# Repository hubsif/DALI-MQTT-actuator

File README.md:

# DALI-MQTT-actuator
An Arduino (Pro Mini) driven DALI actuator and MQTT gateway

More and documentation to follow ...

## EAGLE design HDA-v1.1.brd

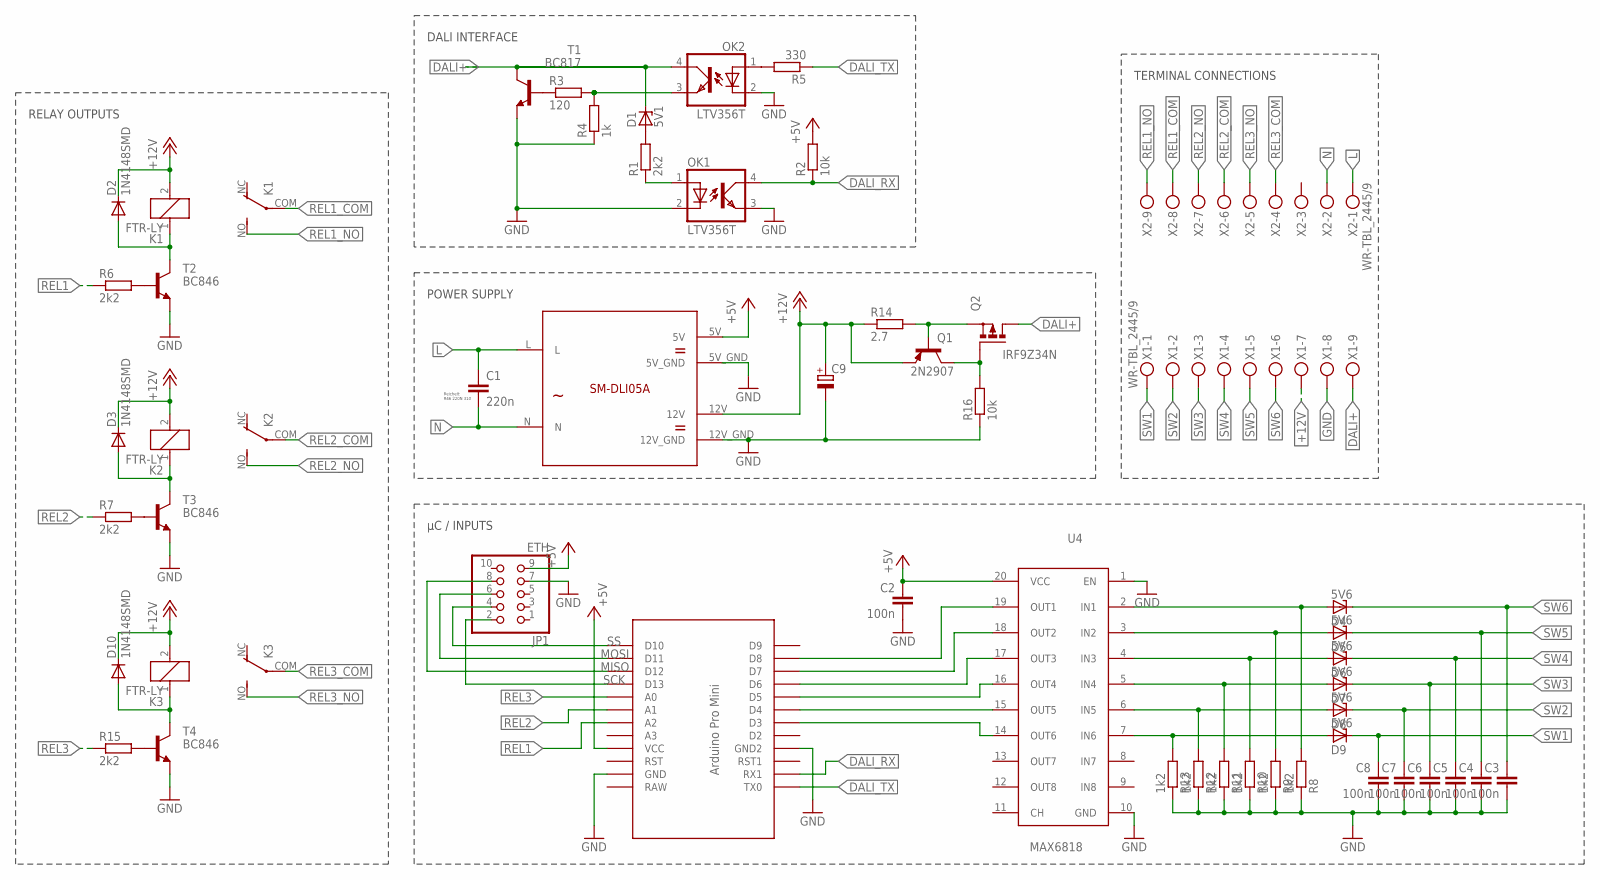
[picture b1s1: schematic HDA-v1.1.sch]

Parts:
C1: 220n; ECQUAAF224
C2, C3, C4, C5, C6, C7, C8: 100n; C1206K
C9: CPOL-EUSMCE; SMC_E
D1: 5V1; SOD80C
D2, D3, D10: 1N4148SMD; SOD80C
D4, D5, D6, D7, D8, D9: 5V6; SOD80C
JP1: ETH; 2X05
K1, K2, K3: FTR-LY; PE-FORM-C
OK1, OK2: LTV356T; SOP-4-2.54
Q1: 2N2907; SOT23-BEC
Q2: IRF9Z34N; TO220BV
R1, R6, R7, R15: 2k2; R1206
R2, R16: 10k; R1206
R3: 120; R1206
R4: 1k; R1206
R5: 330; R1206
R8, R9, R10, R11, R12, R13: 1k2; R1206
R14: 2.7; R1206
T1: BC817; SOT23-BEC
T2, T3, T4: BC846; SOT23
U1: SM-DLI05A
U2: ABK-PRO-MINI
U4: MAX6818; SSOP20
X1, X2: WR-TBL_2445/9

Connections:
+5V: C2.1, JP1.9, R2.2, U1.5V, U2.VCC, U4.20 (VCC)
+12V: C9.+, D2.C, D3.C, D10.C, K1.2, K2.2, K3.2, Q1.E, R14.1, U1.12V, X1.7
DALI+: D1.C, OK2.4 (COL), Q2.D, T1.C, X1.9
DALI_RX: OK1.4 (COL), R2.1, U2.RX1
DALI_TX: R5.1, U2.TX0
GND: C2.2, C3.2, C4.2, C5.2, C6.2, C7.2, C8.2, C9.-, JP1.7, OK1.2 (C), OK1.3 (EMIT), OK2.2 (C), R4.1, R8.1, R9.1, R10.1, R11.1, R12.1, R13.1, R16.1, T1.E, T2.2 (E), T3.2 (E), T4.2 (E), U1.5V_GND, U1.12V_GND, U2.GND, U2.GND1 (GND2), U4.1 (EN), U4.10 (GND), X1.8
L: C1.1, U1.L, X2.1
MISO: JP1.8, U2.D12
MOSI: JP1.6, U2.D11
N: C1.2, U1.N, X2.2
unnamed: D1.A, R1.2
unnamed: OK1.1 (A), R1.1
unnamed: Q1.B, Q2.S, R14.2
unnamed: R3.1, T1.B
unnamed: OK2.3 (EMIT), R3.2, R4.2
unnamed: Q1.C, Q2.G, R16.2
unnamed: OK2.1 (A), R5.2
unnamed: R15.2, T4.1 (B)
unnamed: R6.2, T2.1 (B)
unnamed: R7.2, T3.1 (B)
unnamed: D3.A, K2.1, T3.3 (C)
unnamed: D8.A, R12.2, U4.6 (IN5)
unnamed: D2.A, K1.1, T2.3 (C)
unnamed: D9.A, R13.2, U4.7 (IN6)
unnamed: D4.A, R8.2, U4.2 (IN1)
unnamed: D5.A, R9.2, U4.3 (IN2)
unnamed: D6.A, R10.2, U4.4 (IN3)
unnamed: D7.A, R11.2, U4.5 (IN4)
unnamed: D10.A, K3.1, T4.3 (C)
unnamed: U2.D5, U4.16 (OUT4)
unnamed: U2.D6, U4.17 (OUT3)
unnamed: U2.D7, U4.18 (OUT2)
unnamed: U2.D8, U4.19 (OUT1)
unnamed: U2.D4, U4.15 (OUT5)
unnamed: U2.D3, U4.14 (OUT6)
REL1: R6.1, U2.A2
REL1_COM: K1.COM, X2.8
REL1_NO: K1.NO (S), X2.9
REL2: R7.1, U2.A1
REL2_COM: K2.COM, X2.6
REL2_NO: K2.NO (S), X2.7
REL3: R15.1, U2.A0
REL3_COM: K3.COM, X2.4
REL3_NO: K3.NO (S), X2.5
SCK: JP1.2, U2.D13
SS: JP1.4, U2.D10
SW1: C8.1, D9.C, X1.1
SW2: C7.1, D8.C, X1.2
SW3: C6.1, D7.C, X1.3
SW4: C5.1, D6.C, X1.4
SW5: C4.1, D5.C, X1.5
SW6: C3.1, D4.C, X1.6

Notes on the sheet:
Reichelt: R46 220N 310
DALI INTERFACE
POWER SUPPLY
RELAY OUTPUTS
µC / INPUTS
TERMINAL CONNECTIONS

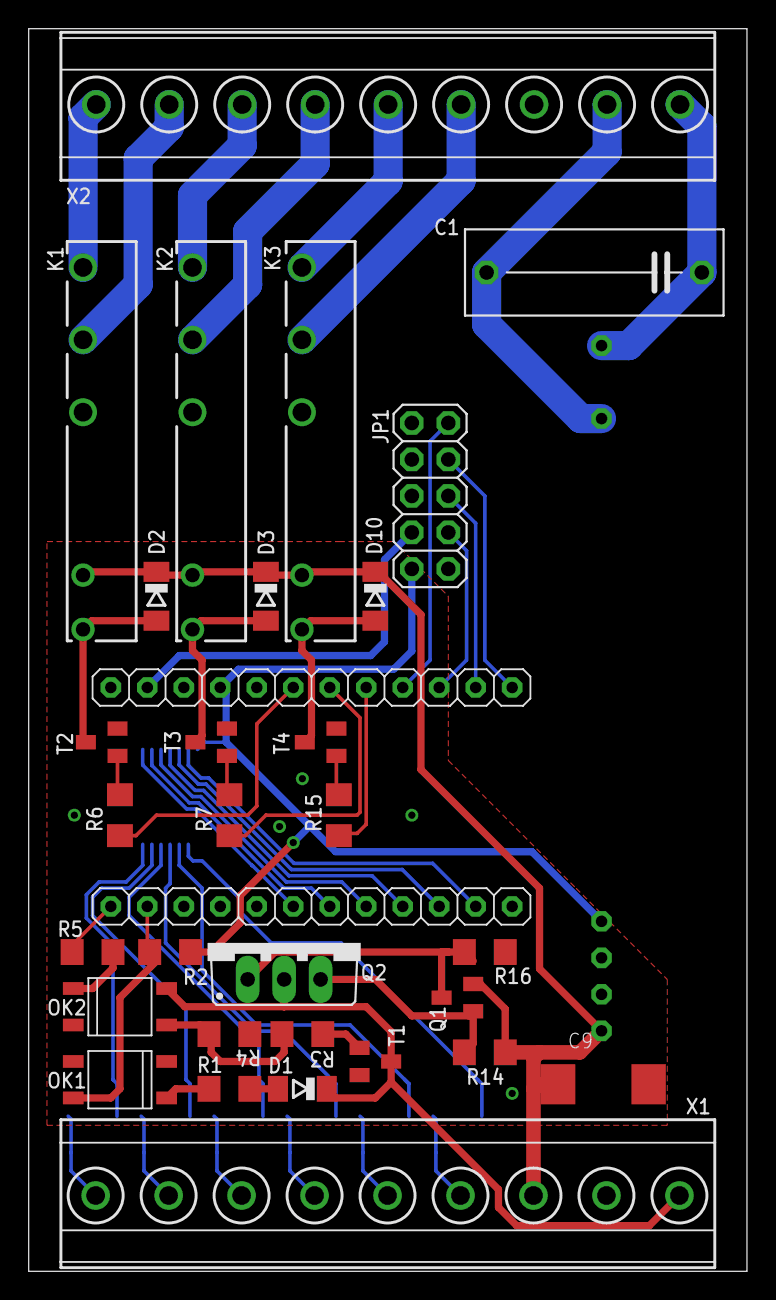
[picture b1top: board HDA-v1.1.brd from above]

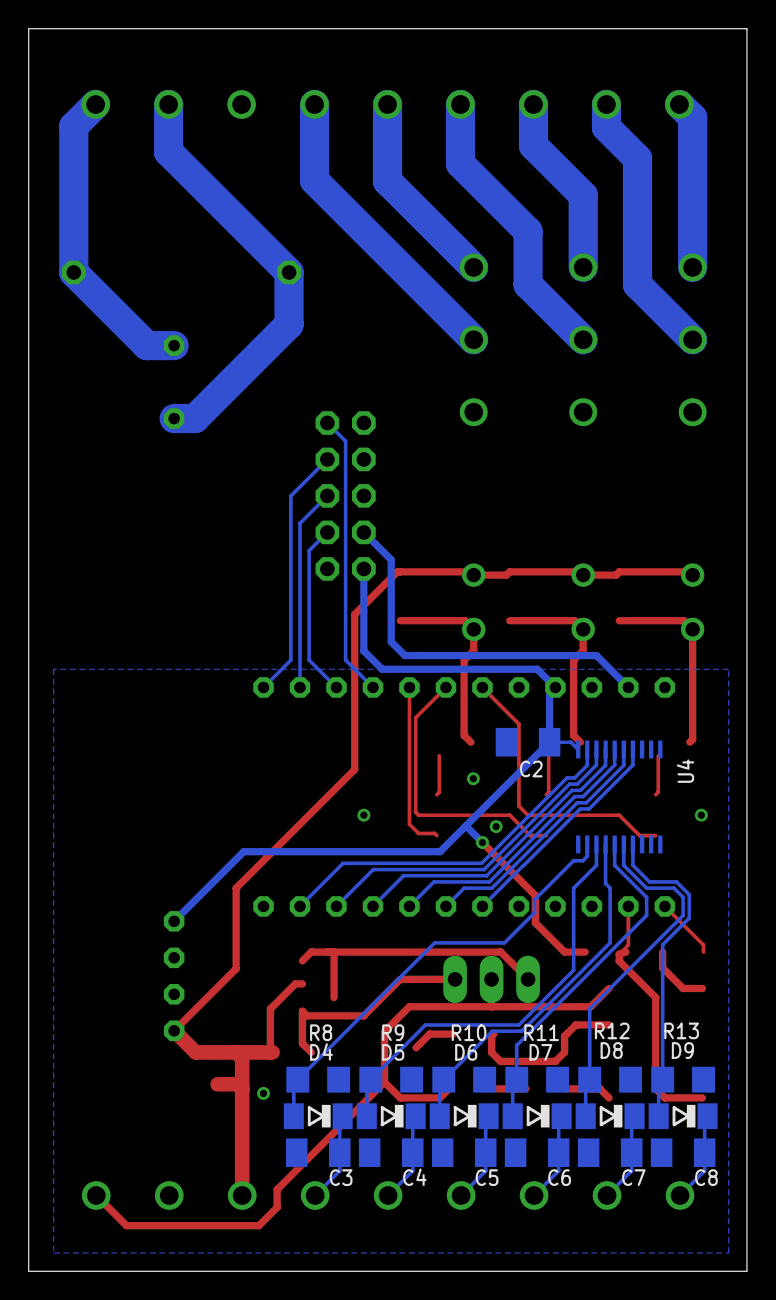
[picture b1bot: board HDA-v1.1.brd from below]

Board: 2 copper layers, 50.0 x 86.5 mm, 52 parts (20 on the bottom side), 52 nets.

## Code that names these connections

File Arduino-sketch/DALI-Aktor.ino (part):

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  group addresses are converted to come after short addresses by adding 64
  which results in addresses being 0-63 for short addresses and 64-79 for group addresses
  80 to 95 are reserved for scenes support
  relays are addressed starting from 96, i.e. REL1=96, REL2=97, REL3=98

*/

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// ---------------

// DALI rx and tx pins
const byte DALI_TX_PIN = 1;
const byte DALI_RX_PIN = 0;

// relay output pins
const byte RELAY_PINS[] = { A2, A1, A0 };
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
  wdt_enable(WDTO_8S); // enable watchdog

  Dali.begin(DALI_TX_PIN, DALI_RX_PIN); // start DALI

  timer.every(BUTTON_SAMPLING_RATE, read_buttons_timerCallback, (void*) 0); // start button polling

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
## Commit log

2023-02-09 Upload Eagle files
2023-02-09 Rename HDA-v1.1.brd to schematics/Eagle/HDA-v1.1.brd
2023-02-09 Rename HDA-v1.1.sch to schematics/Eagle/HDA-v1.1.sch
2023-02-09 Rename Max68x.lbr to schematics/Eagle/Max68x.lbr
2023-02-09 Rename bauteile.lbr to schematics/Eagle/bauteile.lbr
